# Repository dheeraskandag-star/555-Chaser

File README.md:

# 555-Chaser
it is a simple 555 timer chaser. I have placed 10 led's around a batman logo.I will be able to control the speed of the flashing leds using a potentiometer.

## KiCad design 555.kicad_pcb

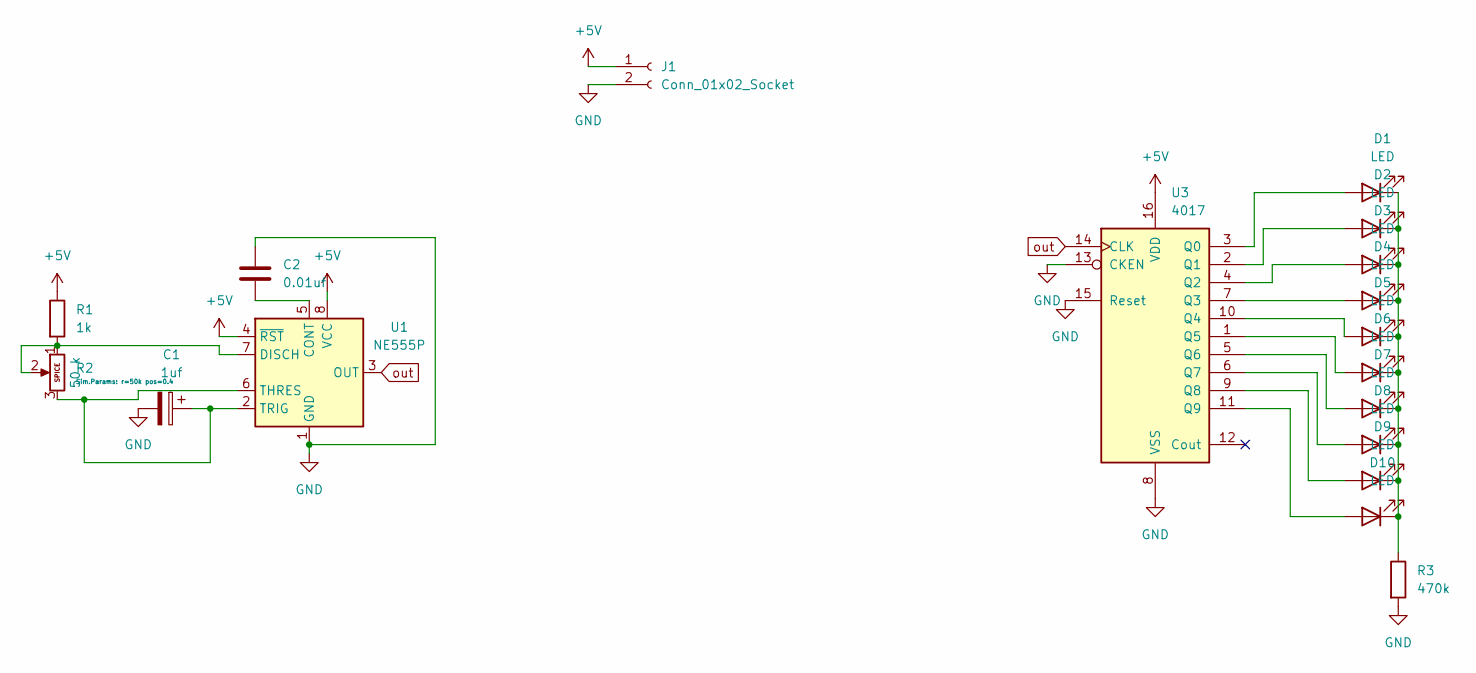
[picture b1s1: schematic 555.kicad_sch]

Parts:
C1: 1uf; CP_Radial_D5.0mm_P2.00mm
C2: 0.01uf; C_Disc_D7.5mm_W2.5mm_P5.00mm
D1, D2, D3, D4, D5, D6, D7, D8, D9, D10: LED; LED_D3.0mm
J1: Conn_01x02_Socket; PinHeader_1x02_P2.54mm_Vertical
R1: 1k; R_Axial_DIN0207_L6.3mm_D2.5mm_P7.62mm_Horizontal
R2: 50 k; Potentiometer_Vishay_T93YA_Vertical
R3: 470k; R_Axial_DIN0207_L6.3mm_D2.5mm_P7.62mm_Horizontal
U1: NE555P; DIP-8_W7.62mm
U3: 4017; N16

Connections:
+5V: J1.1, R1.1, U1.4 (~RST), U1.8 (VCC), U3.16 (VDD)
GND: C1.2, C2.1, J1.2, R3.2, U1.1 (GND), U3.8 (VSS), U3.13 (CKEN), U3.15 (Reset)
unnamed: D1.2 (A), U3.3 (Q0)
unnamed: D1.1 (K), D2.1 (K), D3.1 (K), D4.1 (K), D5.1 (K), D6.1 (K), D7.1 (K), D8.1 (K), D9.1 (K), D10.1 (K), R3.1
unnamed: D2.2 (A), U3.2 (Q1)
unnamed: D3.2 (A), U3.4 (Q2)
unnamed: D4.2 (A), U3.7 (Q3)
unnamed: D5.2 (A), U3.10 (Q4)
unnamed: D6.2 (A), U3.1 (Q5)
unnamed: D7.2 (A), U3.5 (Q6)
unnamed: D8.2 (A), U3.6 (Q7)
unnamed: D9.2 (A), U3.9 (Q8)
unnamed: D10.2 (A), U3.11 (Q9)
unnamed: C2.2, U1.5 (CONT)
unnamed: R1.2, R2.1, R2.2, U1.7 (DISCH)
unnamed: C1.1, R2.3, U1.2 (TRIG), U1.6 (THRES)
out: U1.3 (OUT), U3.14 (CLK)

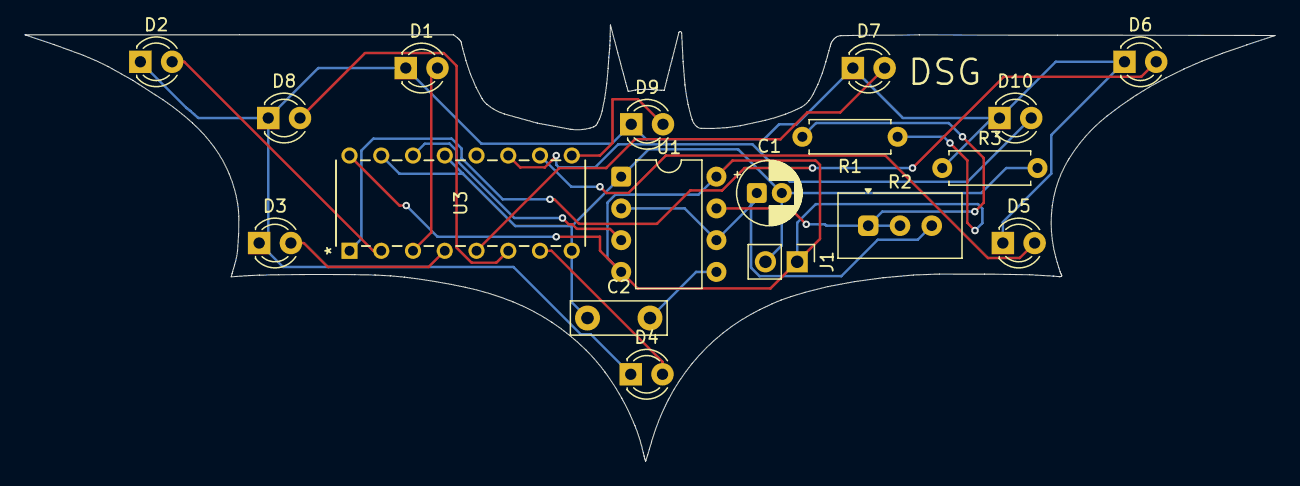
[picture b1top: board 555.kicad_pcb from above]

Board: 2 copper layers, 100.0 x 34.9 mm, 18 parts (0 on the bottom side), 17 nets.

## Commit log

2026-04-09 Rename batman.zip to gerber.zip
